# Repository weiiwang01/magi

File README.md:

> [!WARNING]  
> The magi project is still heavily in progress right now.
> A new version of magi is in the works.

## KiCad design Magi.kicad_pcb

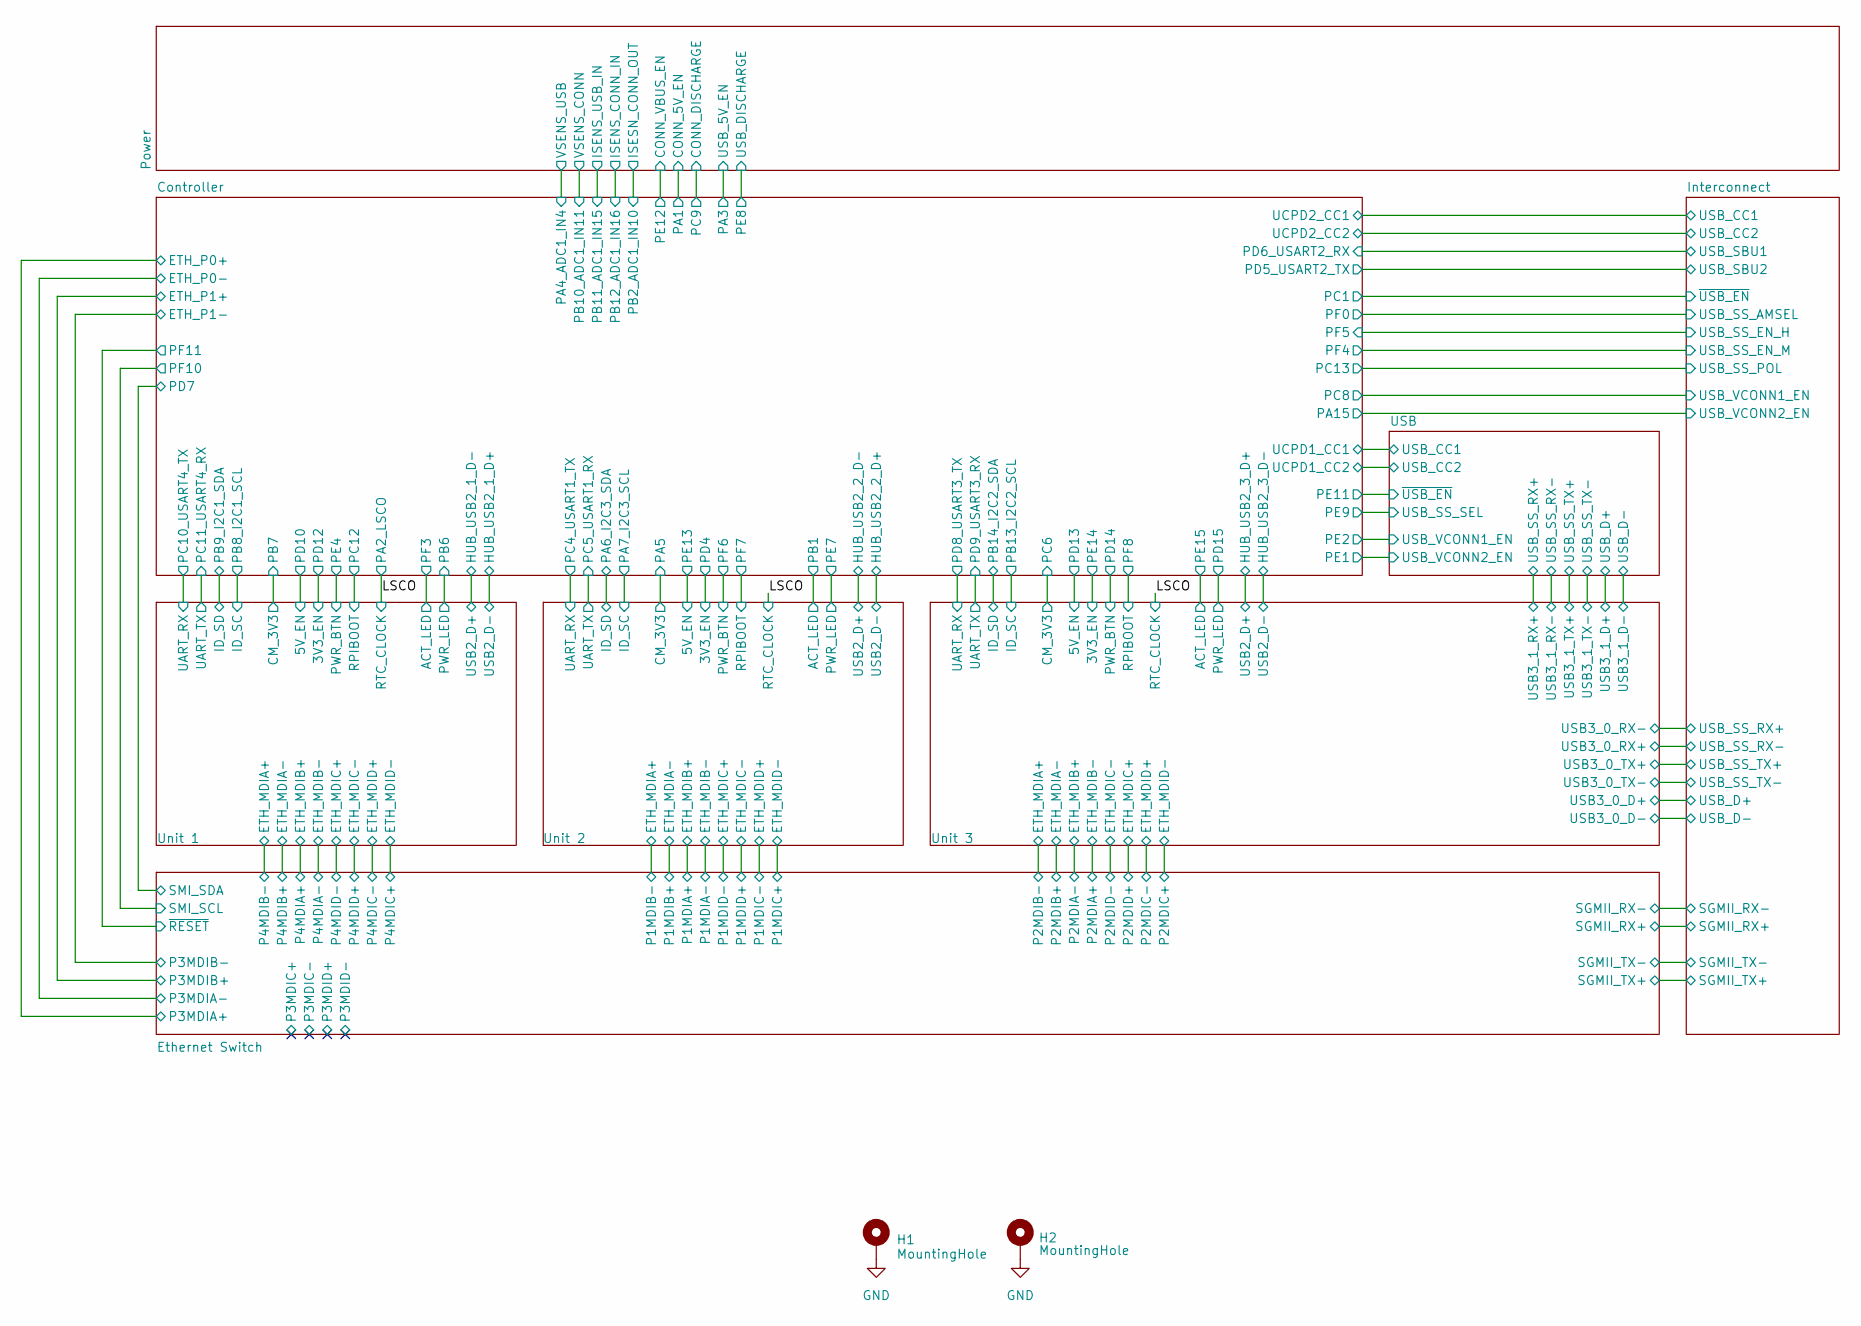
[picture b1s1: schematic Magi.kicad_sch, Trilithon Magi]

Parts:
H1, H2: MountingHole; MOUNTING-HOLE

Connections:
GND: H1.1 (1_1), H2.1 (1_1); also elsewhere on the board

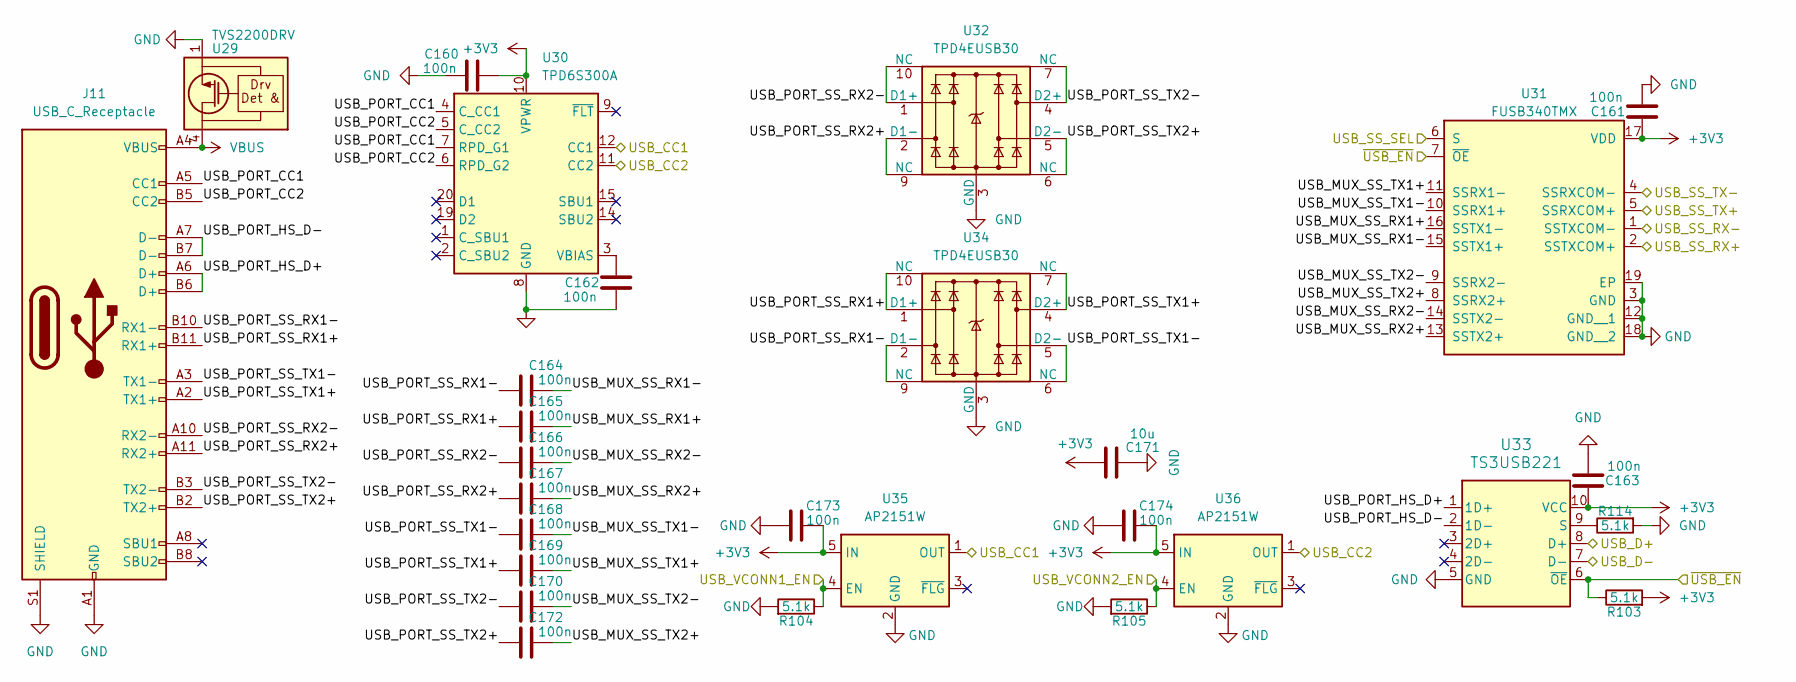
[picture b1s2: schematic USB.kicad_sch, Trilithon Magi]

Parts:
C160, C161, C162, C163, C164, C165, C166, C167, C168, C169, C170, C172, C173, C174: 100n; C_0402_1005Metric; MPN CL05B104KB54PNC; LCSC C307331
C171: 10u; C_0603_1608Metric; MPN CL10A106MA8NRNC; LCSC C96446
J11: USB_C_Receptacle; USB-C-SMD_TYPE-C-GT-USB-7007C; MPN GT-USB-9007A; LCSC C48533148
R103, R104, R105, R114: 5.1k; R_0402_1005Metric; MPN 0402WGF5101TCE; LCSC C25905
U29: TVS2200DRV; WSON-6-1EP_2x2mm_P0.65mm_EP1x1.6mm; MPN TVS2200DRVR; LCSC C523793
U30: TPD6S300A; WQFN-20-1EP_3x3mm_P0.4mm_EP1.7x1.7mm_ThermalVias; MPN TPD6S300A; LCSC C2876380
U31: FUSB340TMX; QFN-18-1EP_2x2.8mm_P0.4mm_EP1.05x1.85mm; MPN FUSB340TMX; LCSC C478457
U32, U34: TPD4EUSB30; USON-10_2.5x1.0mm_P0.5mm; MPN TPD4EUSB30DQAR; LCSC C90627
U33: TS3USB221; Texas_UQFN-10_1.5x2mm_P0.5mm; MPN TS3USB221ARSER; LCSC C128396
U35, U36: AP2151W; SOT-23-5; MPN AP2151WG-7; LCSC C110464

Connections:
+3V3: C160.1, C161.1, C163.1, C171.1, C173.1, C174.1, R103.2, U30.10 (VPWR), U31.17 (VDD), U33.10 (VCC), U35.5 (IN), U36.5 (IN); also elsewhere on the board
/Controller/PE1: R105.1, U36.4 (EN); also elsewhere on the board
/Controller/PE2: R104.1, U35.4 (EN); also elsewhere on the board
/Controller/PE9: U31.6 (S); also elsewhere on the board
/Controller/PE11: R103.1, U31.7 (~OE), U33.6 (~OE); also elsewhere on the board
/Controller/UCPD1_CC1: U30.12 (CC1), U35.1 (OUT); also elsewhere on the board
/Controller/UCPD1_CC2: U30.11 (CC2), U36.1 (OUT); also elsewhere on the board
/USB/USB_D+: U33.8 (D+); also elsewhere on the board
/USB/USB_D-: U33.7 (D-); also elsewhere on the board
/USB/USB_MUX_SS_RX1+: C165.2, U31.16 (SSTX1-)
/USB/USB_MUX_SS_RX1-: C164.2, U31.15 (SSTX1+)
/USB/USB_MUX_SS_RX2+: C167.2, U31.13 (SSTX2+)
/USB/USB_MUX_SS_RX2-: C166.2, U31.14 (SSTX2-)
/USB/USB_MUX_SS_TX1+: C169.2, U31.11 (SSRX1-)
/USB/USB_MUX_SS_TX1-: C168.2, U31.10 (SSRX1+)
/USB/USB_MUX_SS_TX2+: C172.2, U31.8 (SSRX2+)
/USB/USB_MUX_SS_TX2-: C170.2, U31.9 (SSRX2-)
/USB/USB_PORT_CC1: J11.A5 (CC1), U30.4 (C_CC1), U30.7 (RPD_G1)
/USB/USB_PORT_CC2: J11.B5 (CC2), U30.5 (C_CC2), U30.6 (RPD_G2)
/USB/USB_PORT_HS_D+: J11.A6 (D+), J11.B6 (D+), U33.1 (1D+)
/USB/USB_PORT_HS_D-: J11.A7 (D-), J11.B7 (D-), U33.2 (1D-)
/USB/USB_PORT_SS_RX1+: C165.1, J11.B11 (RX1+), U34.1 (D1+), U34.10 (NC)
/USB/USB_PORT_SS_RX1-: C164.1, J11.B10 (RX1-), U34.2 (D1-), U34.9 (NC)
/USB/USB_PORT_SS_RX2+: C167.1, J11.A11 (RX2+), U32.2 (D1-), U32.9 (NC)
/USB/USB_PORT_SS_RX2-: C166.1, J11.A10 (RX2-), U32.1 (D1+), U32.10 (NC)
/USB/USB_PORT_SS_TX1+: C169.1, J11.A2 (TX1+), U34.4 (D2+), U34.7 (NC)
/USB/USB_PORT_SS_TX1-: C168.1, J11.A3 (TX1-), U34.5 (D2-), U34.6 (NC)
/USB/USB_PORT_SS_TX2+: C172.1, J11.B2 (TX2+), U32.5 (D2-), U32.6 (NC)
/USB/USB_PORT_SS_TX2-: C170.1, J11.B3 (TX2-), U32.4 (D2+), U32.7 (NC)
/USB/USB_SS_RX+: U31.2 (SSTXCOM+); also elsewhere on the board
/USB/USB_SS_RX-: U31.1 (SSTXCOM-); also elsewhere on the board
/USB/USB_SS_TX+: U31.5 (SSRXCOM+); also elsewhere on the board
/USB/USB_SS_TX-: U31.4 (SSRXCOM-); also elsewhere on the board
GND: C160.2, C161.2, C162.2, C163.2, C171.2, C173.2, C174.2, J11.A1 (GND), J11.A12 (GND), J11.B1 (GND), J11.B12 (GND), J11.S1 (SHIELD), R104.2, R105.2, R114.2, U29.1 (GND), U29.2 (GND), U29.3 (GND), U29.7 (GND), U30.8 (GND), U30.13 (GND), U30.16 (GND), U30.17 (GND), U30.18 (GND), U30.21 (GND), U31.3 (GND), U31.12 (GND__1), U31.18 (GND__2), U31.19 (EP), U32.3 (GND), U32.8 (GND), U33.5 (GND), U34.3 (GND), U34.8 (GND), U35.2 (GND), U36.2 (GND); also elsewhere on the board
unnamed: C162.1, U30.3 (VBIAS)
unnamed: R114.1, U33.9 (S)
VBUS: J11.A4 (VBUS), J11.A9 (VBUS), J11.B4 (VBUS), J11.B9 (VBUS), U29.4 (IN), U29.5 (IN), U29.6 (IN); also elsewhere on the board

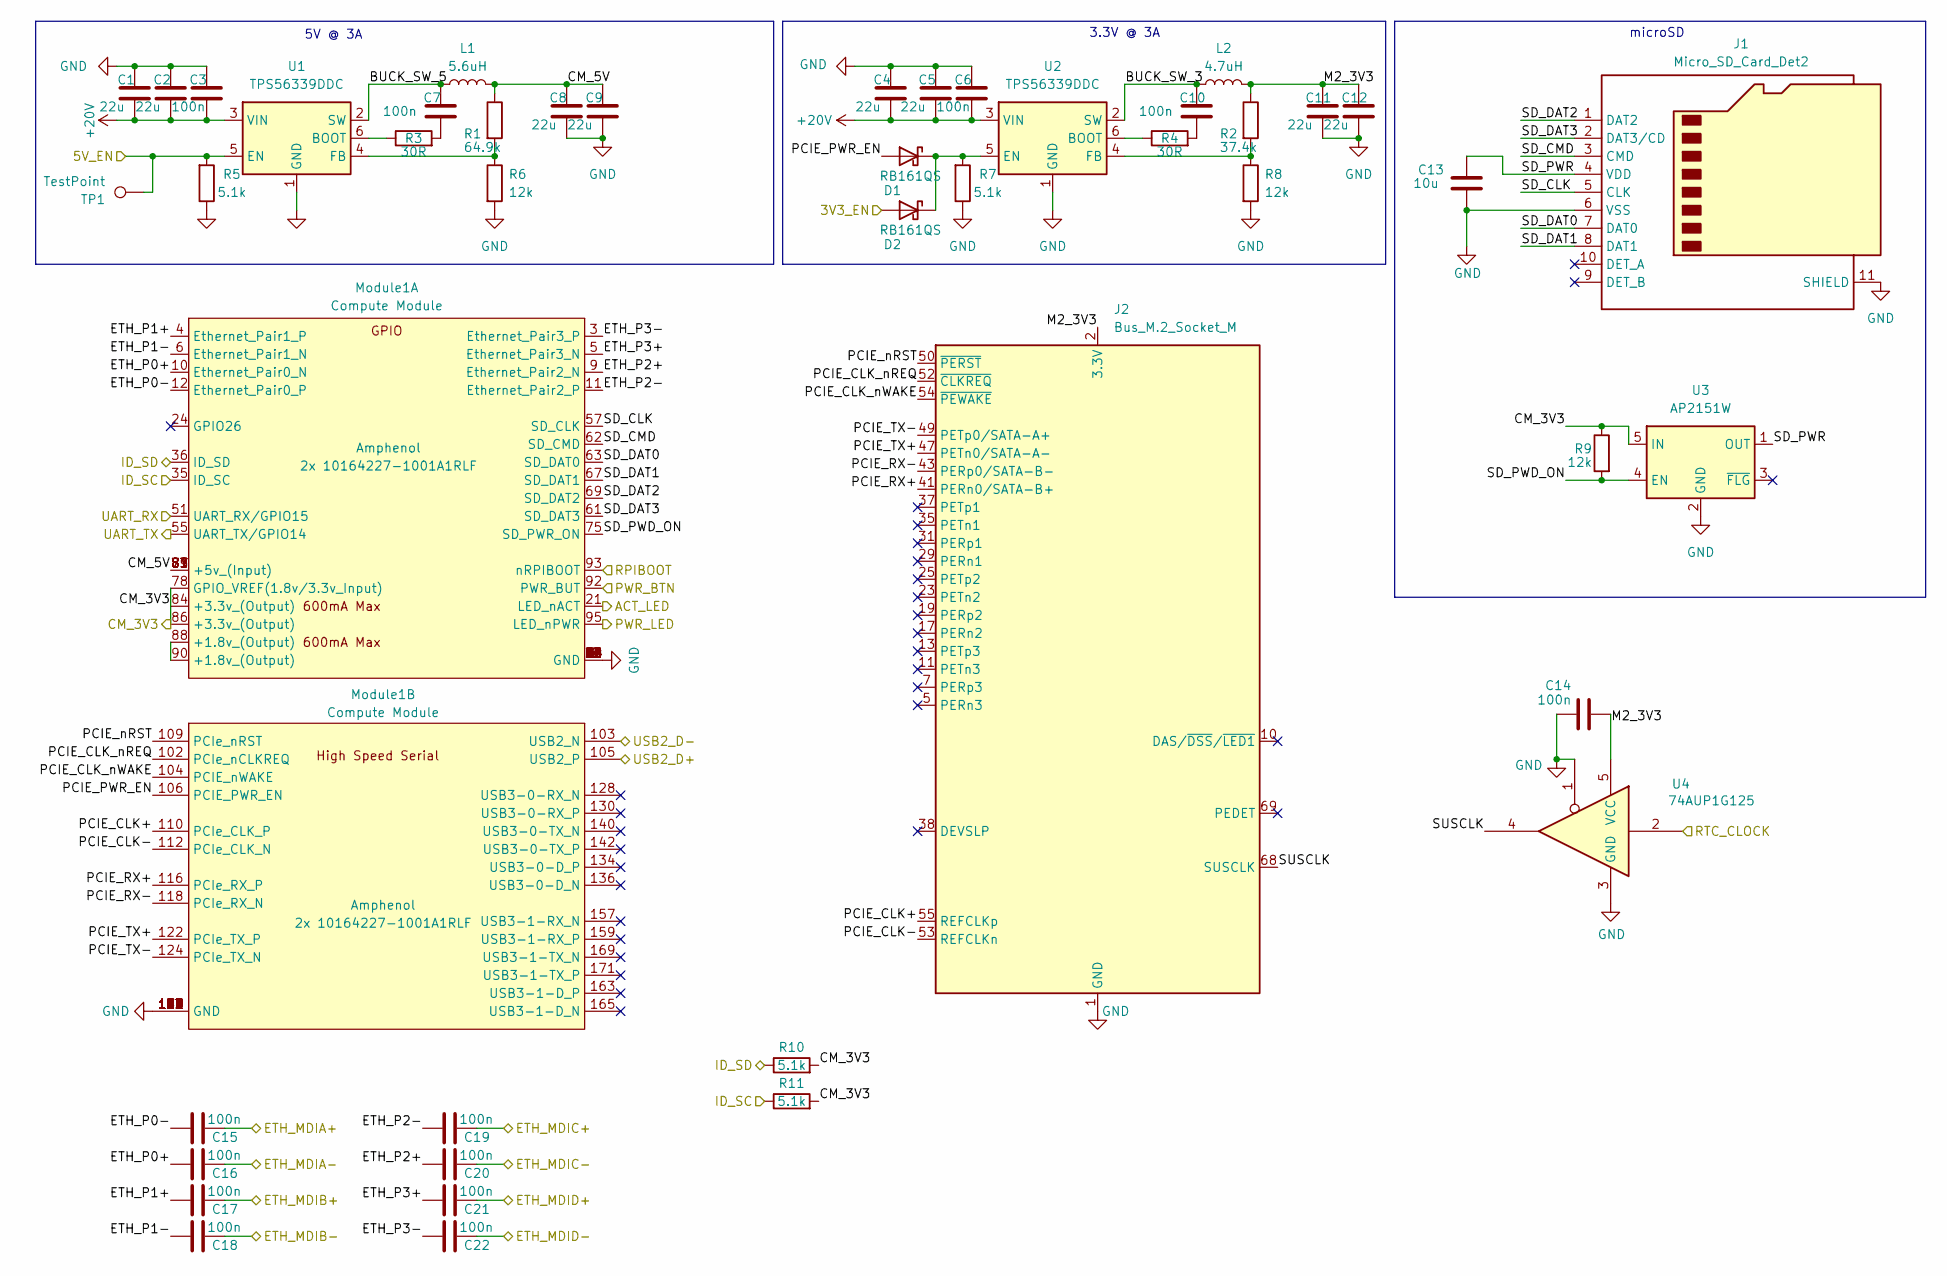
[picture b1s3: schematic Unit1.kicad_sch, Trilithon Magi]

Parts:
C1, C2, C4, C5, C8, C9, C11, C12: 22u; C_0805_2012Metric; MPN CL21A226MAQNNNE; LCSC C45783
C3, C6, C7, C10, C14, C15, C16, C17, C18, C19, C20, C21, C22: 100n; C_0402_1005Metric; MPN CL05B104KB54PNC; LCSC C307331
C13: 10u; C_0603_1608Metric; MPN CL10A106MA8NRNC; LCSC C96446
D1, D2: RB161QS; D_SOD-882; MPN RB161QS-40; LCSC C28646385
J1: Micro_SD_Card_Det2; SDCARD_MOLEX_503398-1892; MPN 5033981892; LCSC C428492
J2: Bus_M.2_Socket_M; CONN-SMD_APCI0146-P001A; MPN APCI0146-P001A; LCSC C841645
L1: 5.6uH; L_Changjiang_FTC404030S; MPN FTC404030S5R6MBCA; LCSC C53436374
L2: 4.7uH; L_Changjiang_FTC404030S; MPN FTC404030S4R7MGCA; LCSC C39676083
Module1: Compute Module; Raspberry-Pi-4-Compute-Module
R1: 64.9k; R_0402_1005Metric; MPN ERJ2RKF6492X; LCSC C416566
R2: 37.4k; R_0402_1005Metric; MPN RC0402FR-0737K4L; LCSC C185422
R3, R4: 30R; R_0402_1005Metric; MPN 0402WGF300JTCE; LCSC C270617
R5, R7, R10, R11: 5.1k; R_0402_1005Metric; MPN 0402WGF5101TCE; LCSC C25905
R6, R8, R9: 12k; R_0402_1005Metric; MPN 0402WGF1202TCE; LCSC C25752
TP1: TestPoint; TestPoint_Pad_D1.5mm
U1, U2: TPS56339DDC; SOT-23-6; MPN TPS56339DDCR; LCSC C2071106
U3: AP2151W; SOT-23-5; MPN AP2151WG-7; LCSC C110464
U4: 74AUP1G125; Texas_X2SON-5_0.8x0.8mm_P0.48mm; MPN SN74AUP1G125DPWR; LCSC C2861319

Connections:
+20V: C1.2, C2.2, C3.2, C4.2, C5.2, C6.2, U1.3 (VIN), U2.3 (VIN); also elsewhere on the board
/Controller/HUB_USB2_1_D+: Module1.103 (USB2_N); also elsewhere on the board
/Controller/HUB_USB2_1_D-: Module1.105 (USB2_P); also elsewhere on the board
/Controller/PB6: Module1.95 (LED_nPWR); also elsewhere on the board
/Controller/PB8_I2C1_SCL: Module1.35 (ID_SC), R11.1; also elsewhere on the board
/Controller/PB9_I2C1_SDA: Module1.36 (ID_SD), R10.1; also elsewhere on the board
/Controller/PC10_USART4_TX: Module1.51 (UART_RX/GPIO15); also elsewhere on the board
/Controller/PC11_USART4_RX: Module1.55 (UART_TX/GPIO14); also elsewhere on the board
/Controller/PC12: Module1.93 (nRPIBOOT); also elsewhere on the board
/Controller/PD10: R5.2, TP1.1 (1_1), U1.5 (EN); also elsewhere on the board
/Controller/PD12: D2.2 (A); also elsewhere on the board
/Controller/PE4: Module1.92 (PWR_BUT); also elsewhere on the board
/Controller/PF3: Module1.21 (LED_nACT); also elsewhere on the board
/Ethernet Switch/P4MDIA+: C17.1; also elsewhere on the board
/Ethernet Switch/P4MDIA-: C18.1; also elsewhere on the board
/Ethernet Switch/P4MDIB+: C16.1; also elsewhere on the board
/Ethernet Switch/P4MDIB-: C15.1; also elsewhere on the board
/Ethernet Switch/P4MDIC+: C22.1; also elsewhere on the board
/Ethernet Switch/P4MDIC-: C21.1; also elsewhere on the board
/Ethernet Switch/P4MDID+: C20.1; also elsewhere on the board
/Ethernet Switch/P4MDID-: C19.1; also elsewhere on the board
/LSCO: U4.2; also elsewhere on the board
/Unit 1/BUCK_SW_3: C10.1, L2.1, U2.2 (SW)
/Unit 1/BUCK_SW_5: C7.1, L1.1, U1.2 (SW)
/Unit 1/CM_3V3: Module1.78 (GPIO_VREF(1.8v/3.3v_Input)), Module1.84 (+3.3v_(Output)), Module1.86 (+3.3v_(Output)), R9.1, R10.2, R11.2, U3.5 (IN); also elsewhere on the board
/Unit 1/CM_5V: C8.1, C9.1, L1.2, Module1.77 (+5v_(Input)), Module1.79 (+5v_(Input)), Module1.81 (+5v_(Input)), Module1.83 (+5v_(Input)), Module1.85 (+5v_(Input)), Module1.87 (+5v_(Input)), R1.1
/Unit 1/ETH_P0+: C16.2, Module1.10 (Ethernet_Pair0_N)
/Unit 1/ETH_P0-: C15.2, Module1.12 (Ethernet_Pair0_P)
/Unit 1/ETH_P1+: C17.2, Module1.4 (Ethernet_Pair1_P)
/Unit 1/ETH_P1-: C18.2, Module1.6 (Ethernet_Pair1_N)
/Unit 1/ETH_P2+: C20.2, Module1.9 (Ethernet_Pair2_N)
/Unit 1/ETH_P2-: C19.2, Module1.11 (Ethernet_Pair2_P)
/Unit 1/ETH_P3+: C21.2, Module1.5 (Ethernet_Pair3_N)
/Unit 1/ETH_P3-: C22.2, Module1.3 (Ethernet_Pair3_P)
/Unit 1/M2_3V3: C11.1, C12.1, C14.2, J2.2 (3.3V), J2.4 (3.3V), J2.12 (3.3V), J2.14 (3.3V), J2.16 (3.3V), J2.18 (3.3V), J2.70 (3.3V), J2.72 (3.3V), J2.74 (3.3V), L2.2, R2.1, U4.5 (VCC)
/Unit 1/PCIE_CLK+: J2.55 (REFCLKp), Module1.110 (PCIe_CLK_P)
/Unit 1/PCIE_CLK-: J2.53 (REFCLKn), Module1.112 (PCIe_CLK_N)
/Unit 1/PCIE_CLK_nREQ: J2.52 (~CLKREQ), Module1.102 (PCIe_nCLKREQ)
/Unit 1/PCIE_CLK_nWAKE: J2.54 (~PEWAKE), Module1.104 (PCIE_nWAKE)
/Unit 1/PCIE_PWR_EN: D1.2 (A), Module1.106 (PCIE_PWR_EN)
/Unit 1/PCIE_RX+: J2.41 (PERn0/SATA-B+), Module1.116 (PCIe_RX_P)
/Unit 1/PCIE_RX-: J2.43 (PERp0/SATA-B-), Module1.118 (PCIe_RX_N)
/Unit 1/PCIE_TX+: J2.47 (PETn0/SATA-A-), Module1.122 (PCIe_TX_P)
/Unit 1/PCIE_TX-: J2.49 (PETp0/SATA-A+), Module1.124 (PCIe_TX_N)
/Unit 1/PCIE_nRST: J2.50 (~PERST), Module1.109 (PCIe_nRST)
/Unit 1/SD_CLK: J1.5 (CLK), Module1.57 (SD_CLK)
/Unit 1/SD_CMD: J1.3 (CMD), Module1.62 (SD_CMD)
/Unit 1/SD_DAT0: J1.7 (DAT0), Module1.63 (SD_DAT0)
/Unit 1/SD_DAT1: J1.8 (DAT1), Module1.67 (SD_DAT1)
/Unit 1/SD_DAT2: J1.1 (DAT2), Module1.69 (SD_DAT2)
/Unit 1/SD_DAT3: J1.2 (DAT3/CD), Module1.61 (SD_DAT3)
/Unit 1/SD_PWD_ON: Module1.75 (SD_PWR_ON), R9.2, U3.4 (EN)
/Unit 1/SD_PWR: C13.1, J1.4 (VDD), U3.1 (OUT)
/Unit 1/SUSCLK: J2.68 (SUSCLK), U4.4
GND: C1.1, C2.1, C3.1, C4.1, C5.1, C6.1, C8.2, C9.2, C11.2, C12.2, C13.2, C14.1, J1.6 (VSS), J1.11 (SHIELD), J2.1 (GND), J2.3 (GND), J2.9 (GND), J2.15 (GND), J2.21 (GND), J2.27 (GND), J2.33 (GND), J2.39 (GND), J2.45 (GND), J2.51 (GND), J2.57 (GND), J2.71 (GND), J2.73 (GND), J2.75 (GND), Module1.1 (GND), Module1.2 (GND), Module1.7 (GND), Module1.8 (GND), Module1.13 (GND), Module1.14 (GND), Module1.22 (GND), Module1.23 (GND), Module1.32 (GND), Module1.33 (GND), Module1.42 (GND), Module1.43 (GND), Module1.52 (GND), Module1.53 (GND), Module1.59 (GND), Module1.60 (GND), Module1.65 (GND), Module1.66 (GND), Module1.71 (GND), Module1.74 (GND), Module1.98 (GND), Module1.107 (GND), Module1.108 (GND), Module1.113 (GND), Module1.114 (GND), Module1.119 (GND), Module1.120 (GND), Module1.125 (GND), Module1.126 (GND), Module1.131 (GND), Module1.132 (GND), Module1.137 (GND), Module1.138 (GND), Module1.144 (GND), Module1.150 (GND), Module1.155 (GND), Module1.156 (GND), Module1.161 (GND), Module1.162 (GND), Module1.167 (GND), Module1.168 (GND), Module1.173 (GND), Module1.174 (GND), Module1.179 (GND), Module1.180 (GND), Module1.185 (GND), Module1.186 (GND), Module1.191 (GND), Module1.192 (GND), Module1.197 (GND), Module1.198 (GND), R5.1, R6.2, R7.1, R8.2, U1.1 (GND), U2.1 (GND), U3.2 (GND), U4.1, U4.3 (GND); also elsewhere on the board
unnamed: C7.2, R3.2
unnamed: C10.2, R4.2
unnamed: D1.1 (K), D2.1 (K), Module1.56 (GPIO3), R7.2, U2.5 (EN)
unnamed: Module1.88 (+1.8v_(Output)), Module1.90 (+1.8v_(Output))
unnamed: R3.1, U1.6 (BOOT)
unnamed: R1.2, R6.1, U1.4 (FB)
unnamed: R4.1, U2.6 (BOOT)
unnamed: R2.2, R8.1, U2.4 (FB)

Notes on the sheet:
5V @ 3A
3.3V @ 3A
microSD

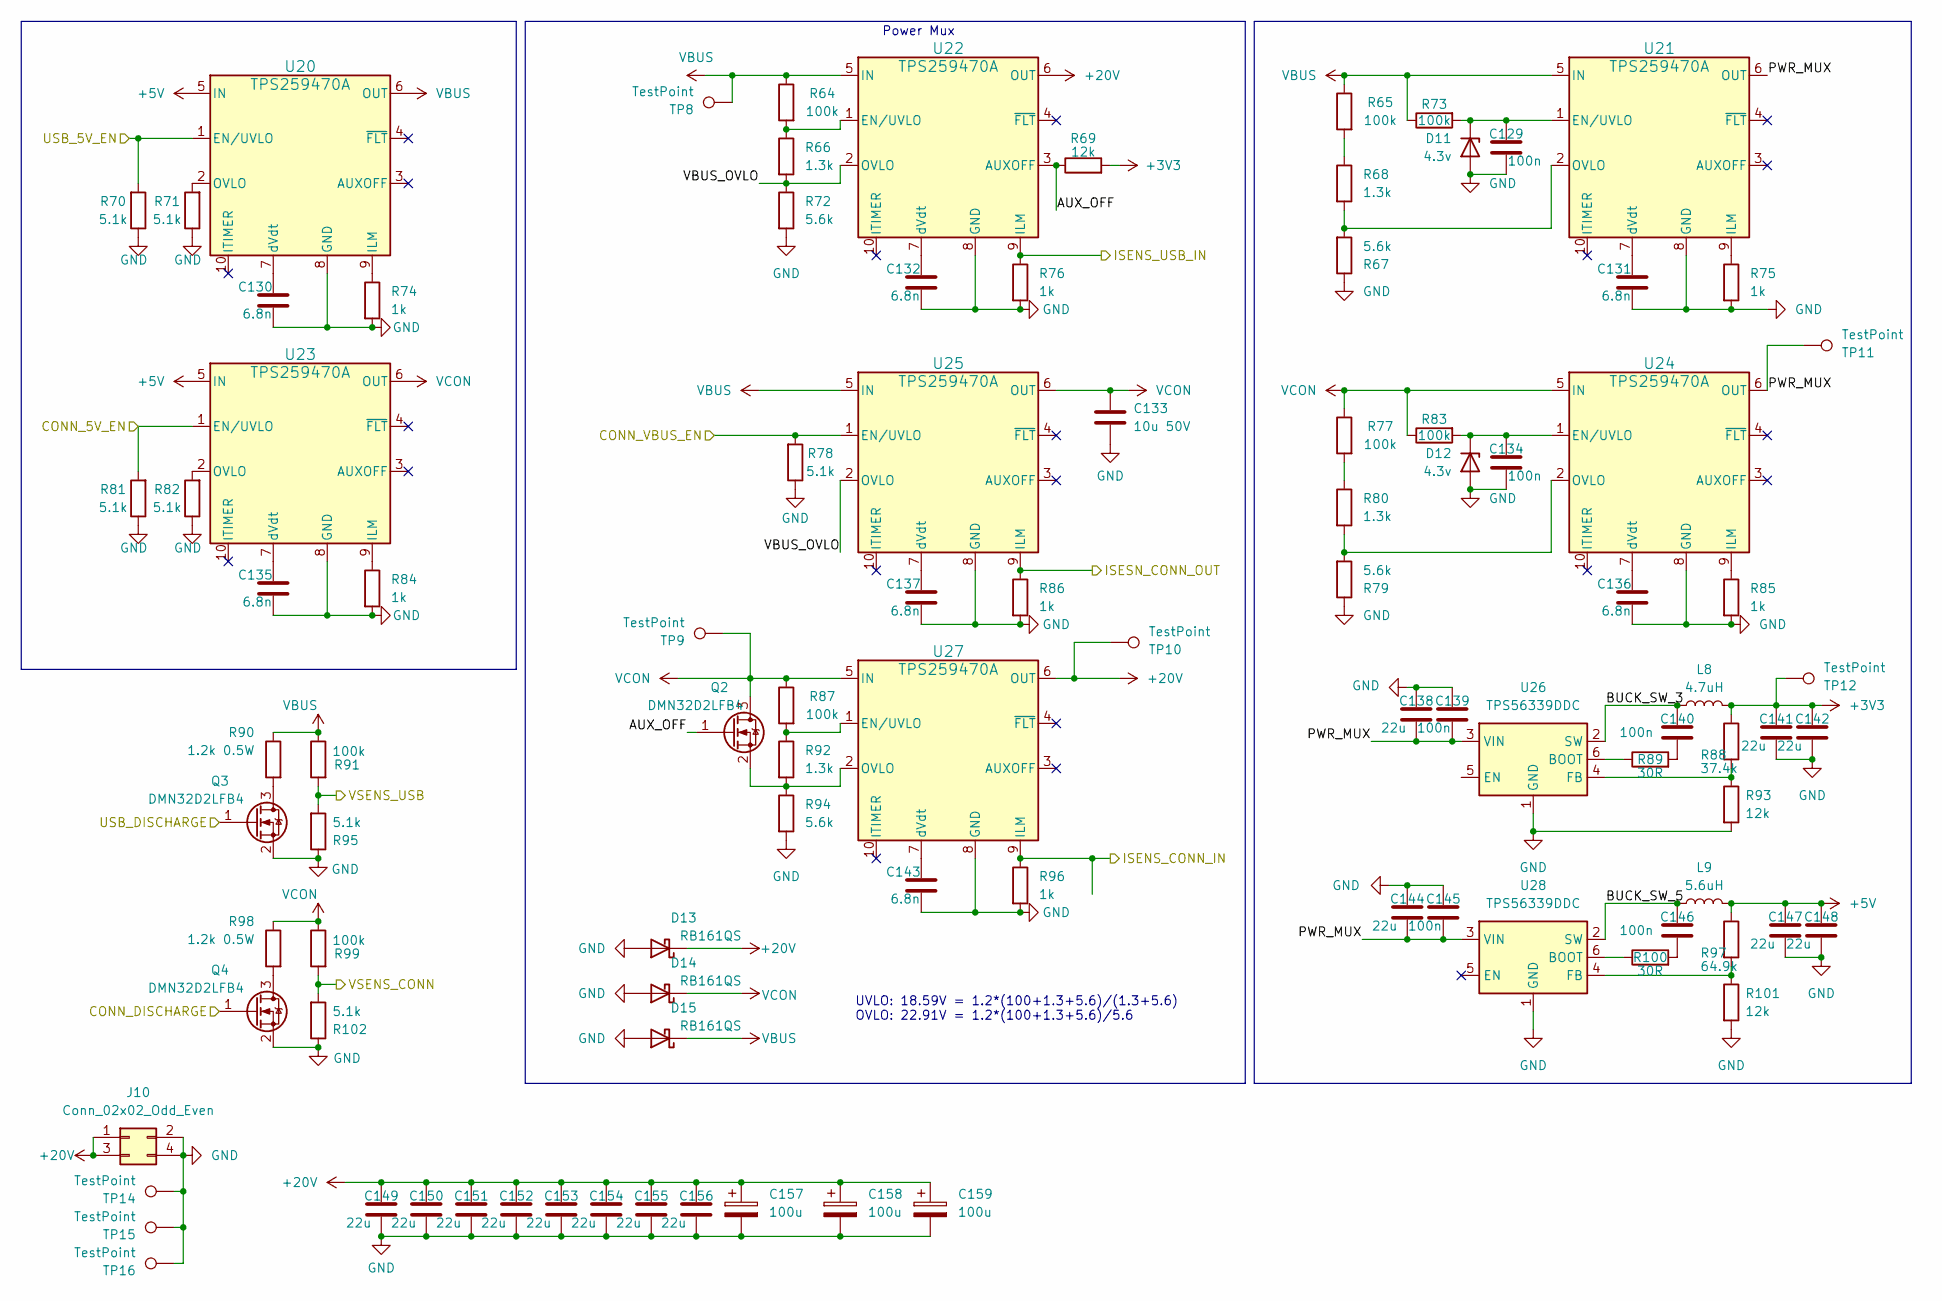
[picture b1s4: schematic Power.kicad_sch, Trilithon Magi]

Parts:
C129, C134, C139, C140, C145, C146: 100n; C_0402_1005Metric; MPN CL05B104KB54PNC; LCSC C307331
C130, C131, C132, C135, C136, C137, C143: 6.8n; C_0402_1005Metric; MPN GRM1555C1H682JE01D; LCSC C1518206
C133: 10u 50V; C_1210_3225Metric; MPN GCM32EC71H106KA03L; LCSC C126612
C138, C141, C142, C144, C147, C148, C149, C150, C151, C152, C153, C154, C155, C156: 22u; C_0805_2012Metric; MPN CL21A226MAQNNNE; LCSC C45783
C157, C158, C159: 100u; CP_Elec_6.3x5.7; MPN A768EB107M1ELAS036; LCSC C1517616
D11, D12: 4.3v; D_SOD-523; MPN BZX584C4V3; LCSC C46641695
D13, D14, D15: RB161QS; D_SOD-882; MPN RB161QS-40; LCSC C28646385
J10: Conn_02x02_Odd_Even; PinHeader_2x02_P2.54mm_Vertical
L8: 4.7uH; L_Changjiang_FTC404030S; MPN FTC404030S4R7MGCA; LCSC C39676083
L9: 5.6uH; L_Changjiang_FTC404030S; MPN FTC404030S5R6MBCA; LCSC C53436374
Q2, Q3, Q4: DMN32D2LFB4; Diodes_DFN1006-3; MPN DMN32D2LFB4-7; LCSC C151382
R64, R65, R73, R77, R83, R87, R91, R99: 100k; R_0402_1005Metric; MPN 0402WGF1003TCE; LCSC C25741
R66, R68, R80, R92: 1.3k; R_0402_1005Metric; MPN 0402WGF1301TCE; LCSC C25866
R67, R72, R79, R94: 5.6k; R_0402_1005Metric; MPN RC0402FR-075K6L; LCSC C409920
R69, R93, R101: 12k; R_0402_1005Metric; MPN 0402WGF1202TCE; LCSC C25752
R70, R71, R78, R81, R82, R95, R102: 5.1k; R_0402_1005Metric; MPN 0402WGF5101TCE; LCSC C25905
R74, R75, R76, R84, R85, R86, R96: 1k; R_0402_1005Metric; MPN 0402WGF1001TCE; LCSC C11702
R88: 37.4k; R_0402_1005Metric; MPN RC0402FR-0737K4L; LCSC C185422
R89, R100: 30R; R_0402_1005Metric; MPN 0402WGF300JTCE; LCSC C270617
R90, R98: 1.2k 0.5W; R_1206_3216Metric; MPN FRP1206F1201TS; LCSC C7468365
R97: 64.9k; R_0402_1005Metric; MPN ERJ2RKF6492X; LCSC C416566
TP8, TP9, TP10, TP11, TP12, TP14, TP15, TP16: TestPoint; TestPoint_Pad_D1.5mm
U20, U21, U22, U23, U24, U25, U27: TPS259470A; RPW0010A-MFG; MPN TPS259470ARPWR; LCSC C3662799
U26, U28: TPS56339DDC; SOT-23-6; MPN TPS56339DDCR; LCSC C2071106

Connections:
+3V3: C141.1, C142.1, L8.2, R69.2, R88.1, TP12.1 (1_1); also elsewhere on the board
+5V: C147.1, C148.1, L9.2, R97.1, U20.5 (IN), U23.5 (IN); also elsewhere on the board
+20V: C149.1, C150.1, C151.1, C152.1, C153.1, C154.1, C155.1, C156.1, C157.1, C158.1, C159.1, D13.1 (K), J10.1, J10.3, TP10.1 (1_1), U22.6 (OUT), U27.6 (OUT); also elsewhere on the board
/Controller/PA1: R81.2, U23.1 (EN/UVLO); also elsewhere on the board
/Controller/PA3: R70.2, U20.1 (EN/UVLO); also elsewhere on the board
/Controller/PA4_ADC1_IN4: R91.2, R95.2; also elsewhere on the board
/Controller/PB2_ADC1_IN10: R86.1, U25.9 (ILM); also elsewhere on the board
/Controller/PB10_ADC1_IN11: R99.2, R102.2; also elsewhere on the board
/Controller/PB11_ADC1_IN15: R76.1, U22.9 (ILM); also elsewhere on the board
/Controller/PB12_ADC1_IN16: R96.1, U27.9 (ILM); also elsewhere on the board
/Controller/PC9: Q4.1 (G); also elsewhere on the board
/Controller/PE8: Q3.1 (G); also elsewhere on the board
/Controller/PE12: R78.2, U25.1 (EN/UVLO); also elsewhere on the board
/Power/AUX_OFF: Q2.1 (G), R69.1, U22.3 (AUXOFF)
/Power/BUCK_SW_3: C140.1, L8.1, U26.2 (SW)
/Power/BUCK_SW_5: C146.1, L9.1, U28.2 (SW)
/Power/PWR_MUX: C138.2, C139.2, C144.2, C145.2, TP11.1 (1_1), U21.6 (OUT), U24.6 (OUT), U26.3 (VIN), U28.3 (VIN)
/Power/VBUS_OVLO: R66.2, R72.1, U22.2 (OVLO), U25.2 (OVLO)
GND: C129.2, C130.2, C131.2, C132.2, C133.2, C134.2, C135.2, C136.2, C137.2, C138.1, C139.1, C141.2, C142.2, C143.2, C144.1, C145.1, C147.2, C148.2, C149.2, C150.2, C151.2, C152.2, C153.2, C154.2, C155.2, C156.2, C157.2, C158.2, C159.2, D11.2 (A), D12.2 (A), D13.2 (A), D14.2 (A), D15.2 (A), J10.2, J10.4, Q3.2 (S), Q4.2 (S), R67.1, R70.1, R71.1, R72.2, R74.2, R75.2, R76.2, R78.1, R79.1, R81.1, R82.1, R84.2, R85.2, R86.2, R93.2, R94.2, R95.1, R96.2, R101.2, R102.1, TP14.1 (1_1), TP15.1 (1_1), TP16.1 (1_1), U20.8 (GND), U21.8 (GND), U22.8 (GND), U23.8 (GND), U24.8 (GND), U25.8 (GND), U26.1 (GND), U27.8 (GND), U28.1 (GND); also elsewhere on the board
unnamed: C140.2, R89.2
unnamed: C146.2, R100.2
unnamed: C129.1, D11.1 (K), R73.2, U21.1 (EN/UVLO)
unnamed: C134.1, D12.1 (K), R83.2, U24.1 (EN/UVLO)
unnamed: Q2.2 (S), R92.2, R94.1, U27.2 (OVLO)
unnamed: Q3.3 (D), R90.2
unnamed: Q4.3 (D), R98.2
unnamed: R65.2, R68.1
unnamed: R77.2, R80.1
unnamed: R74.1, U20.9 (ILM)
unnamed: R71.2, U20.2 (OVLO)
unnamed: C130.1, U20.7 (dVdt)
unnamed: R75.1, U21.9 (ILM)
unnamed: R67.2, R68.2, U21.2 (OVLO)
unnamed: C131.1, U21.7 (dVdt)
unnamed: R64.2, R66.1, U22.1 (EN/UVLO)
unnamed: C132.1, U22.7 (dVdt)
unnamed: R84.1, U23.9 (ILM)
unnamed: R82.2, U23.2 (OVLO)
unnamed: C135.1, U23.7 (dVdt)
unnamed: R85.1, U24.9 (ILM)
unnamed: R79.2, R80.2, U24.2 (OVLO)
unnamed: C136.1, U24.7 (dVdt)
unnamed: C137.1, U25.7 (dVdt)
unnamed: R89.1, U26.6 (BOOT)
unnamed: R88.2, R93.1, U26.4 (FB)
unnamed: R87.2, R92.1, U27.1 (EN/UVLO)
unnamed: C143.1, U27.7 (dVdt)
unnamed: R100.1, U28.6 (BOOT)
unnamed: R97.2, R101.1, U28.4 (FB)
VBUS: D15.1 (K), R64.1, R65.1, R73.1, R90.1, R91.1, TP8.1 (1_1), U20.6 (OUT), U21.5 (IN), U22.5 (IN), U25.5 (IN); also elsewhere on the board
VCON: C133.1, D14.1 (K), Q2.3 (D), R77.1, R83.1, R87.1, R98.1, R99.1, TP9.1 (1_1), U23.6 (OUT), U24.5 (IN), U25.6 (OUT), U27.5 (IN); also elsewhere on the board

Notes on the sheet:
UVLO: 18.59V = 1.2*(100+1.3+5.6)/(1.3+5.6) OVLO: 22.91V = 1.2*(100+1.3+5.6)/5.6
Power Mux
